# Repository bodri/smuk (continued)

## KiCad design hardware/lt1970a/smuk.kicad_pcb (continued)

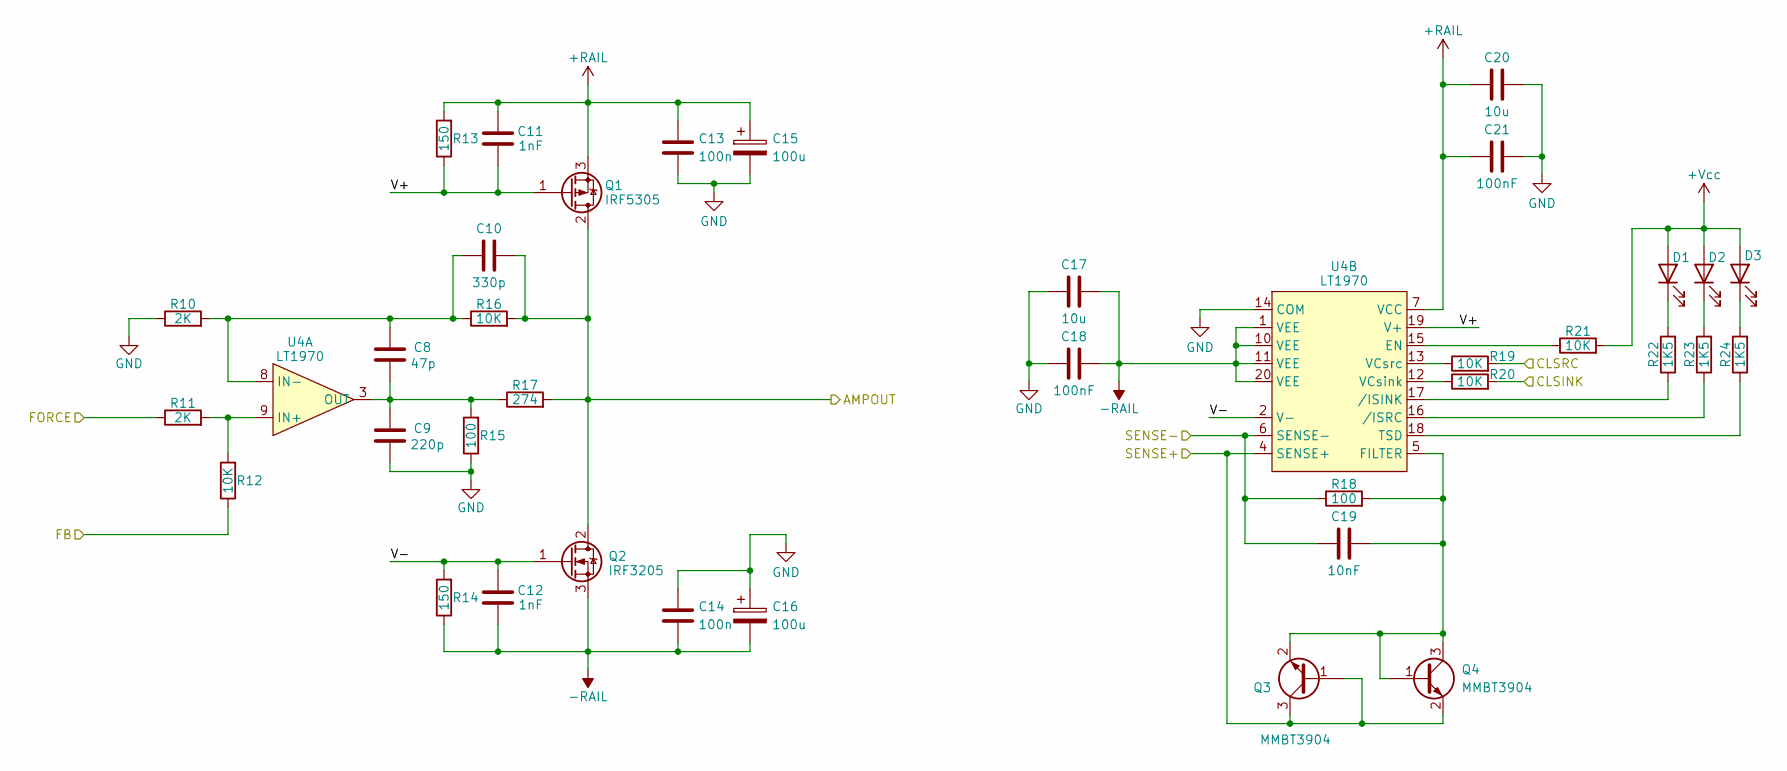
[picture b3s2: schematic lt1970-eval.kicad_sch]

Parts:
C8: 47p; C_0603_1608Metric
C9: 220p; C_0603_1608Metric
C10: 330p; C_0603_1608Metric
C11, C12: 1nF; C_0603_1608Metric
C13, C14: 100n; C_0603_1608Metric
C15, C16: 100u; C_Elec_10x10.2
C17, C20: 10u; C_0603_1608Metric
C18, C21: 100nF; C_0603_1608Metric
C19: 10nF; C_0603_1608Metric
D1, D2, D3: LED; LED_0603_1608Metric
Q1: IRF5305; TO-220-3_Vertical
Q2: IRF3205; TO-220-3_Vertical
Q3, Q4: MMBT3904; SOT-323_SC-70
R10, R11: 2K; R_0603_1608Metric
R12, R16, R19, R20, R21: 10K; R_0603_1608Metric
R13, R14: 150; R_0603_1608Metric
R15, R18: 100; R_0603_1608Metric
R17: 274; R_0603_1608Metric
R22, R23, R24: 1K5; R_0603_1608Metric
U4: LT1970

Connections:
/LT1970A amplifier/AMPOUT: C10.1, Q1.2 (D), Q2.2 (D), R16.2, R17.2; also elsewhere on the board
/LT1970A amplifier/CLSINK: R20.2; also elsewhere on the board
/LT1970A amplifier/CLSRC: R19.2; also elsewhere on the board
/LT1970A amplifier/FB: R12.1; also elsewhere on the board
/LT1970A amplifier/FORCE: R11.1; also elsewhere on the board
/LT1970A amplifier/SENSE+: Q3.1 (B), Q3.3 (C), Q4.2 (E), U4.4 (SENSE+); also elsewhere on the board
/LT1970A amplifier/V+: C11.2, Q1.1 (G), R13.1, U4.19 (V+)
/LT1970A amplifier/V-: C12.1, Q2.1 (G), R14.2, U4.2 (V-)
GND: C9.2, C13.2, C14.1, C15.2, C16.1, C17.2, C18.2, C19.1, C20.2, C21.2, R10.1, R15.1, R18.1, U4.6 (SENSE-), U4.14 (COM); also elsewhere on the board
unnamed: D1.1 (K), R22.2
unnamed: D2.1 (K), R23.2
unnamed: D3.1 (K), R24.2
unnamed: C19.2, Q3.2 (E), Q4.1 (B), Q4.3 (C), R18.2, U4.5 (FILTER)
unnamed: R11.2, R12.2, U4.9 (IN+)
unnamed: C8.1, C10.2, R10.2, R16.1, U4.8 (IN-)
unnamed: C8.2, C9.1, R15.2, R17.1, U4.3 (OUT)
unnamed: R21.1, U4.15 (EN)
unnamed: R24.1, U4.18 (TSD)
unnamed: R20.1, U4.12 (VCsink)
unnamed: R19.1, U4.13 (VCsrc)
unnamed: R22.1, U4.17 (/ISINK)
unnamed: R23.1, U4.16 (/ISRC)
VCC: D1.2 (A), D2.2 (A), D3.2 (A), R21.2

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
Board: 2 copper layers, 63 parts (0 on the bottom side), 40 nets, no tracks yet.

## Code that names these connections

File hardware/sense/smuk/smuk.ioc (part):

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Mcu.Name=STM32H503CBUx
Mcu.Package=UFQFPN48
Mcu.UserName=STM32H503CBUx
PA0.GPIOParameters=GPIO_Label
PA0.GPIO_Label=IR2A_M
PA0.Signal=ADCx_INP0
PA1.GPIOParameters=GPIO_Label
PA1.GPIO_Label=IR2A
PA1.Signal=GPIO_Output
PA11.Mode=Asynchronous
PA11.Signal=USART1_RX
PA12.Mode=Asynchronous
PA12.Signal=USART1_TX
PA13(JTMS/SWDIO).Mode=Trace_Asynchronous_SW
PA13(JTMS/SWDIO).Signal=DEBUG_JTMS-SWDIO
PA14(JTCK/SWCLK).Mode=Trace_Asynchronous_SW
PA14(JTCK/SWCLK).Signal=DEBUG_JTCK-SWCLK
PA15(JTDI).Mode=NSS_Signal_Hard_Input
PA15(JTDI).Signal=SPI3_NSS
PA2.GPIOParameters=GPIO_Label
PA2.GPIO_Label=IR100MA_M
PA2.Signal=ADCx_INP14
PA3.GPIOParameters=GPIO_Label
PA3.GPIO_Label=IR100MA
PA3.Signal=GPIO_Output
PA4.GPIOParameters=GPIO_Label
PA4.GPIO_Label=IR10MA_M
PA4.Signal=ADCx_INP18
PA5.GPIOParameters=GPIO_Label
PA5.GPIO_Label=IR10MA
PA5.Signal=GPIO_Output
PA6.GPIOParameters=GPIO_Label
PA6.GPIO_Label=IR1MA_M
PA6.Signal=ADCx_INP3
PA7.GPIOParameters=GPIO_Label
PA7.GPIO_Label=IR1MA
PA7.Signal=GPIO_Output
PA8.GPIOParameters=GPIO_Label
PA8.GPIO_Label=NDRDY_ADC
PA8.Signal=GPXTI8
PA9.GPIOParameters=PinState,GPIO_Label
PA9.GPIO_Label=NRESET_ADC
PA9.PinState=GPIO_PIN_SET
PA9.Signal=GPIO_Output
PB0.GPIOParameters=GPIO_Label
PB0.GPIO_Label=IR100UA_M
PB0.Signal=ADCx_INP9
PB1.GPIOParameters=GPIO_Label
PB1.GPIO_Label=IR100UA
PB1.Signal=GPIO_Output
PB12.GPIOParameters=GPIO_Label
PB12.GPIO_Label=CS_ADC
PB12.Mode=NSS_Signal_Hard_Input
PB12.Signal=SPI2_NSS
PB13.GPIOParameters=GPIO_Label
PB13.GPIO_Label=SCK_ADC
PB13.Mode=Full_Duplex_Master
PB13.Signal=SPI2_SCK
PB14.GPIOParameters=GPIO_Label
PB14.GPIO_Label=MISO_ADC
PB14.Mode=Full_Duplex_Master
PB14.Signal=SPI2_MISO
PB15.GPIOParameters=GPIO_Label
PB15.GPIO_Label=MOSI_ADC
PB15.Mode=Full_Duplex_Master
PB15.Signal=SPI2_MOSI
PB3(JTDO/TRACESWO).Mode=Trace_Asynchronous_SW
PB3(JTDO/TRACESWO).Signal=DEBUG_JTDO-SWO
PB4(NJTRST).GPIOParameters=GPIO_Label
PB4(NJTRST).GPIO_Label=MISO_DAC
PB4(NJTRST).Mode=Full_Duplex_Master
PB4(NJTRST).Signal=SPI3_MISO
PB5.GPIOParameters=GPIO_Label
PB5.GPIO_Label=MOSI_DAC
PB5.Mode=Full_Duplex_Master
PB5.Signal=SPI3_MOSI
PB6.GPIOParameters=PinState,GPIO_Label
PB6.GPIO_Label=NRESET_DAC
PB6.PinState=GPIO_PIN_SET
PB6.Signal=GPIO_Output
PB7.GPIOParameters=GPIO_Label
PB7.GPIO_Label=SCK_DAC
PB7.Mode=Full_Duplex_Master
PB7.Signal=SPI3_SCK
PH0-OSC_IN(PH0).Mode=HSE-External-Oscillator
PH0-OSC_IN(PH0).Signal=RCC_OSC_IN
PH1-OSC_OUT(PH1).Mode=HSE-External-Oscillator
PH1-OSC_OUT(PH1).Signal=RCC_OSC_OUT
RCC.HSE_VALUE=16000000
RCC.SYSCLKFreq_VALUE=240000000
RCC.SYSCLKSource=RCC_SYSCLKSOURCE_PLLCLK
board=custom

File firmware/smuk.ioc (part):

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Mcu.Name=STM32H503RBTx
Mcu.Package=LQFP64
Mcu.UserName=STM32H503RBTx
PA0.GPIOParameters=GPIO_Speed,PinState,GPIO_Label
PA0.GPIO_Label=IR1MA
PA0.GPIO_Speed=GPIO_SPEED_FREQ_VERY_HIGH
PA0.PinState=GPIO_PIN_SET
PA0.Signal=GPIO_Output
PA1.GPIOParameters=GPIO_Speed,PinState,GPIO_Label
PA1.GPIO_Label=IR10MA
PA1.GPIO_Speed=GPIO_SPEED_FREQ_VERY_HIGH
PA1.PinState=GPIO_PIN_SET
PA1.Signal=GPIO_Output
PA13(JTMS/SWDIO).Mode=Trace_Asynchronous_SW
PA13(JTMS/SWDIO).Signal=DEBUG_JTMS-SWDIO
PA14(JTCK/SWCLK).Mode=Trace_Asynchronous_SW
PA14(JTCK/SWCLK).Signal=DEBUG_JTCK-SWCLK
PA5.Signal=COMP_DAC12_group
PA6.Mode=Full_Duplex_Master
PA6.Signal=SPI1_MISO
PB0.GPIOParameters=GPIO_Speed,PinState,GPIO_Label
PB0.GPIO_Label=IR2A
PB0.GPIO_Speed=GPIO_SPEED_FREQ_VERY_HIGH
PB0.PinState=GPIO_PIN_SET
PB0.Signal=GPIO_Output
PB1.GPIOParameters=GPIO_Speed,PinState,GPIO_Label
PB1.GPIO_Label=IR100MA
PB1.GPIO_Speed=GPIO_SPEED_FREQ_VERY_HIGH
PB1.PinState=GPIO_PIN_SET
PB1.Signal=GPIO_Output
PB12.GPIOParameters=GPIO_Label
PB12.GPIO_Label=CALBUS_S0
PB12.Signal=GPIO_Output
PB13.GPIOParameters=GPIO_Label
PB13.GPIO_Label=CALBUS_S1
PB13.Signal=GPIO_Output
PB3(JTDO/TRACESWO).Mode=Trace_Asynchronous_SW
PB3(JTDO/TRACESWO).Signal=DEBUG_JTDO-SWO
PB8.Mode=NSS_Signal_Hard_Output
PB8.Signal=SPI1_NSS
PC12.GPIOParameters=GPIO_Speed,PinState,GPIO_Label
PC12.GPIO_Label=IR100UA
PC12.GPIO_Speed=GPIO_SPEED_FREQ_VERY_HIGH
PC12.PinState=GPIO_PIN_SET
PC12.Signal=GPIO_Output
PC13.Signal=GPXTI13
PC2.GPIOParameters=GPIO_Label
PC2.GPIO_Label=MV_ON
PC2.Signal=GPIO_Output
PC3.GPIOParameters=PinState,GPIO_Label
PC3.GPIO_Label=VRANGE
PC3.PinState=GPIO_PIN_RESET
PC3.Signal=GPIO_Output
PC4.GPIOParameters=PinState,GPIO_Label
PC4.GPIO_Label=ICAL
PC4.PinState=GPIO_PIN_SET
PC4.Signal=GPIO_Output
PC5.Mode=Full_Duplex_Master
PC5.Signal=SPI1_SCK
PC6.GPIOParameters=GPIO_PuPd,GPIO_Label,GPIO_ModeDefaultEXTI
PC6.GPIO_Label=NDRDY
PC6.GPIO_ModeDefaultEXTI=GPIO_MODE_IT_FALLING
PC6.GPIO_PuPd=GPIO_NOPULL
PC6.Signal=GPXTI6
PC7.Mode=Full_Duplex_Master
PC7.Signal=SPI1_MOSI
PC8.GPIOParameters=PinState,GPIO_Label
PC8.GPIO_Label=VCAL
PC8.PinState=GPIO_PIN_SET
PC8.Signal=GPIO_Output
PC9.GPIOParameters=PinState,GPIO_Label
PC9.GPIO_Label=NRESET
PC9.PinState=GPIO_PIN_SET
PC9.Signal=GPIO_Output
RCC.HSE_VALUE=24000000
RCC.SYSCLKFreq_VALUE=244000000
RCC.SYSCLKSource=RCC_SYSCLKSOURCE_PLLCLK
board=NUCLEO-H503RB
boardIOC=true
